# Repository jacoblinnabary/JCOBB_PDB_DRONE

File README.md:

Overview:
This project is a custom power distribution and control board designed for a small personal drone build using the F450 drone frame. The PCB handles high-current battery routing to an external 40A ESC while providing a clean mounting and control platform for an Arduino Nano. The Nano generates PWM signals for the ESC and optionally handles additional sensor inputs or flight-related logic.

Features

High-current power corridor for battery → ESC with support for burst currents up to 40A

Optimized for 1 oz copper using wide pours and via-stitched layers

Supports 12 AWG wire input/output pads

Integrated Arduino Nano footprint for control logic and PWM generation

Optional connectors for signals, auxiliary power, and expansion

Designed entirely in KiCad, with all source files included

Purpose:
This board simplifies wiring, reduces mess, and provides a mechanically solid mounting point for both the microcontroller and the high-current ESC connections in a compact drone platform.

Future changes: Replacing ground and power traces with planes, and adding thermal relief to pads. This will allow for higher currents and easier routing of other traces. Standardizing the distance of the extra pins next to the nano, and matching the distances found on breadboards/protoboards. Ultimately, switching out the Arduino Nano to an STM32 would allow for add ons to be done easier.

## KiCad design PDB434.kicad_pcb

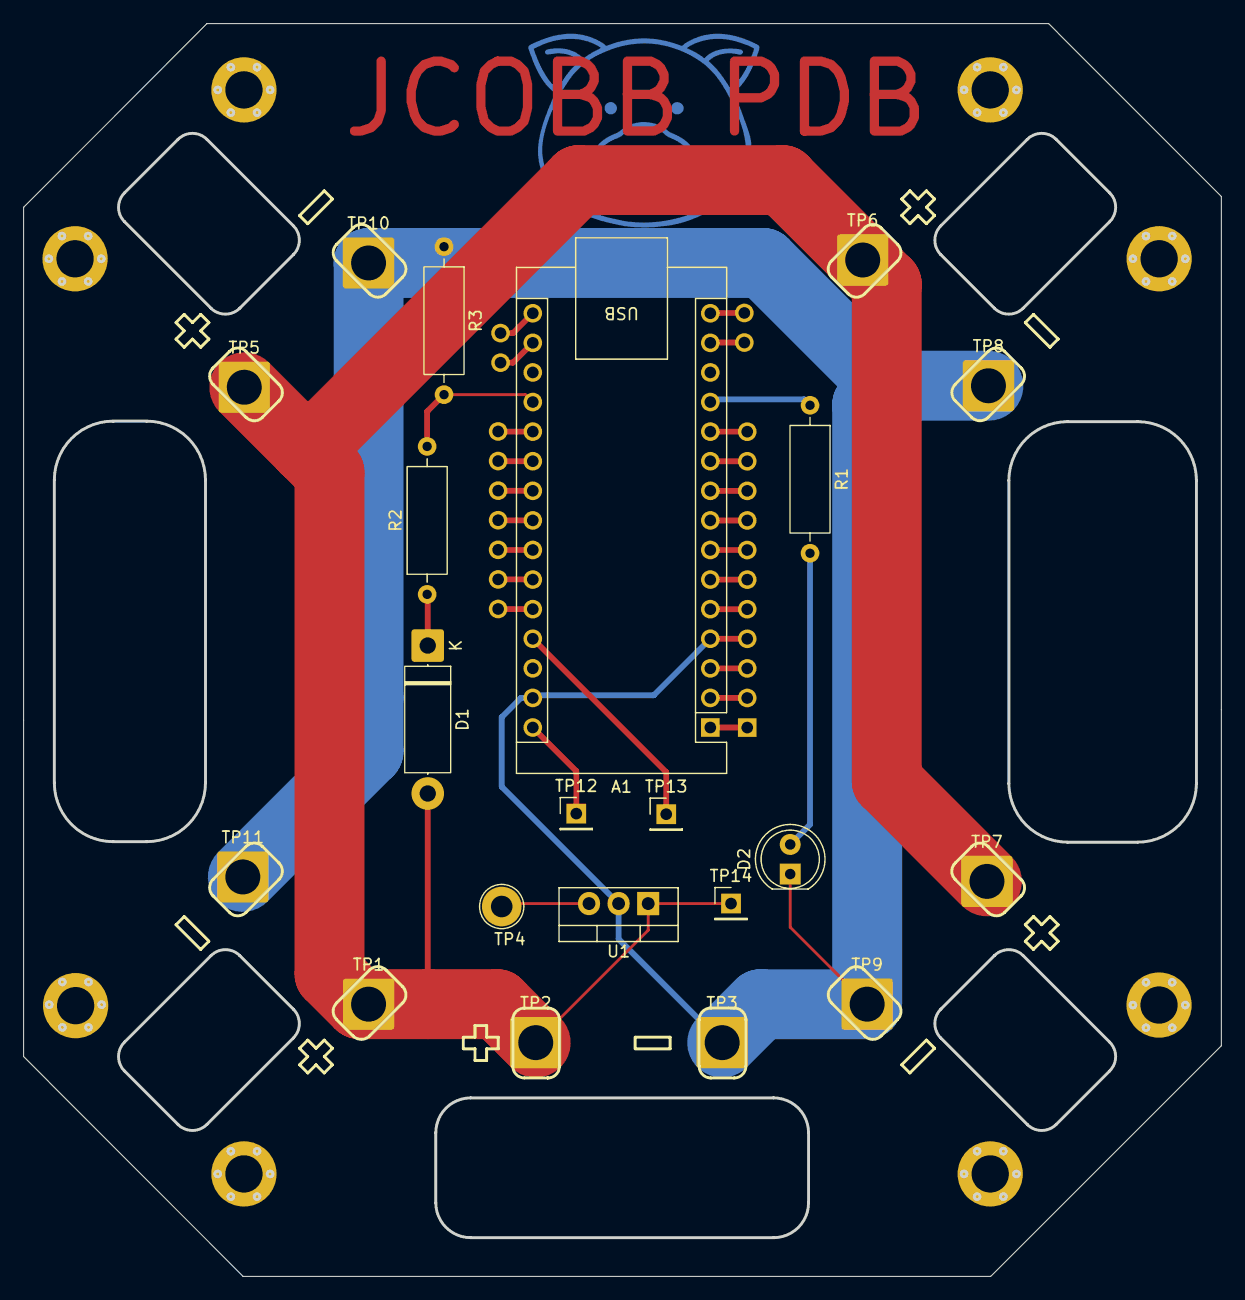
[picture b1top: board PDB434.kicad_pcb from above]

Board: 2 copper layers, 102.6 x 107.3 mm, 21 parts (0 on the bottom side), 9 nets.

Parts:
A1: Arduino_Nano_Every; Arduino_Nano
D1: D; D_5W_P12.70mm_Horizontal
D2: LED; LED_D5.0mm
R1, R2, R3: R_US; R_Axial_DIN0309_L9.0mm_D3.2mm_P12.70mm_Horizontal
TP1: ESC 3+; SolderWire-2.5sqmm_1x01_D2.4mm_OD4.4mm
TP2: Battery +; SolderWire-2.5sqmm_1x01_D2.4mm_OD4.4mm
TP3: Battery -; SolderWire-2.5sqmm_1x01_D2.4mm_OD4.4mm
TP4: TestPoint; TestPoint_Loop_D2.50mm_Drill1.85mm
TP5: ESC 1+; SolderWire-2.5sqmm_1x01_D2.4mm_OD4.4mm
TP6: ESC 2+; SolderWire-2.5sqmm_1x01_D2.4mm_OD4.4mm
TP7: ESC 4+; SolderWire-2.5sqmm_1x01_D2.4mm_OD4.4mm
TP8: ESC 2-; SolderWire-2.5sqmm_1x01_D2.4mm_OD4.4mm
TP9: ESC 4-; SolderWire-2.5sqmm_1x01_D2.4mm_OD4.4mm
TP10: ESC 1-; SolderWire-2.5sqmm_1x01_D2.4mm_OD4.4mm
TP11: ESC 3-; SolderWire-2.5sqmm_1x01_D2.4mm_OD4.4mm
TP12, TP13, TP14: TestPoint; PinHeader_1x01_P2.54mm_Vertical
U1: L7805; TO-220-3_Vertical

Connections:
GND: A1.4 (GND), A1.29 (GND), D2.1 (K), R3.1, TP3.1, TP8.1, TP9.1, TP10.1, TP11.1, U1.2 (GND)
unnamed: A1.27 (+5V), TP13.1
unnamed: A1.19 (A0), R2.2, R3.2
unnamed: A1.12 (D9), R1.1
unnamed: A1.30 (VIN), TP12.1
unnamed: D1.2 (A), TP1.1, TP2.1, TP5.1, TP6.1, TP7.1, TP14.1, U1.1 (IN)
unnamed: D1.1 (K), R2.1
unnamed: D2.2 (A), R1.2
unnamed: TP4.1, U1.3 (OUT)

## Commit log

2025-11-22 Add project overview and features to README
    This README provides an overview of the custom power distribution and control board for a personal drone, detailing its features and purpose.
2025-11-22 Update README formatting and section headers
2025-11-23 Added KiCad FIles
2025-11-23 Add future changes section to README
    Added future changes section outlining planned improvements.
2025-11-23 Enhance README overview with F450 frame details
    Updated project overview to include F450 drone frame.
